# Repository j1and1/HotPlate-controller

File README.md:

# Hotplate reflow controller

This is still a work in progress, and controller code has issues of overshooting the target temperature **use at your own risk.** 

This is a implementation of temperature control of heated plate for reflow soldering.

## Wiring

To make this you will need:
1. Arduino pro mini (or any other microcontroller)
2. Thermal resistor (I used 100k one from my 3d printer spares)
3. 4.7kOhm resistor for temperature resistor pullup
4. 10uF capacitor for stabilizing sensor value
5. Nokia 5510 display module (Or other display module... code might need to be patched for this though)
6. Solid state relay (use solid state relay to avoid arking when Arduino enables disables the output pin)
7. if Arduino runs on 5V you will need additional 5 10k resistors and one 1kOhm resistors on the SPI line ment for display.

## Compiling code

To compile Arduino code you will need few additional libraries.
1. Thermistor library [from here](https://github.com/miguel5612/ThermistorLibrary) or Arduino IDE library section
2. Adafruit PCD8544 library from Arduino IDE library section [or here](https://github.com/adafruit/Adafruit-PCD8544-Nokia-5110-LCD-library). Dont forget to install dependencies for it too.

## Known issues
- Thermal runaway algorithm is ignoring the state of solid state relay output pin
- Controller code does not account for thermal mass of the heater and plate. This will get solved once PID algorithm is added.

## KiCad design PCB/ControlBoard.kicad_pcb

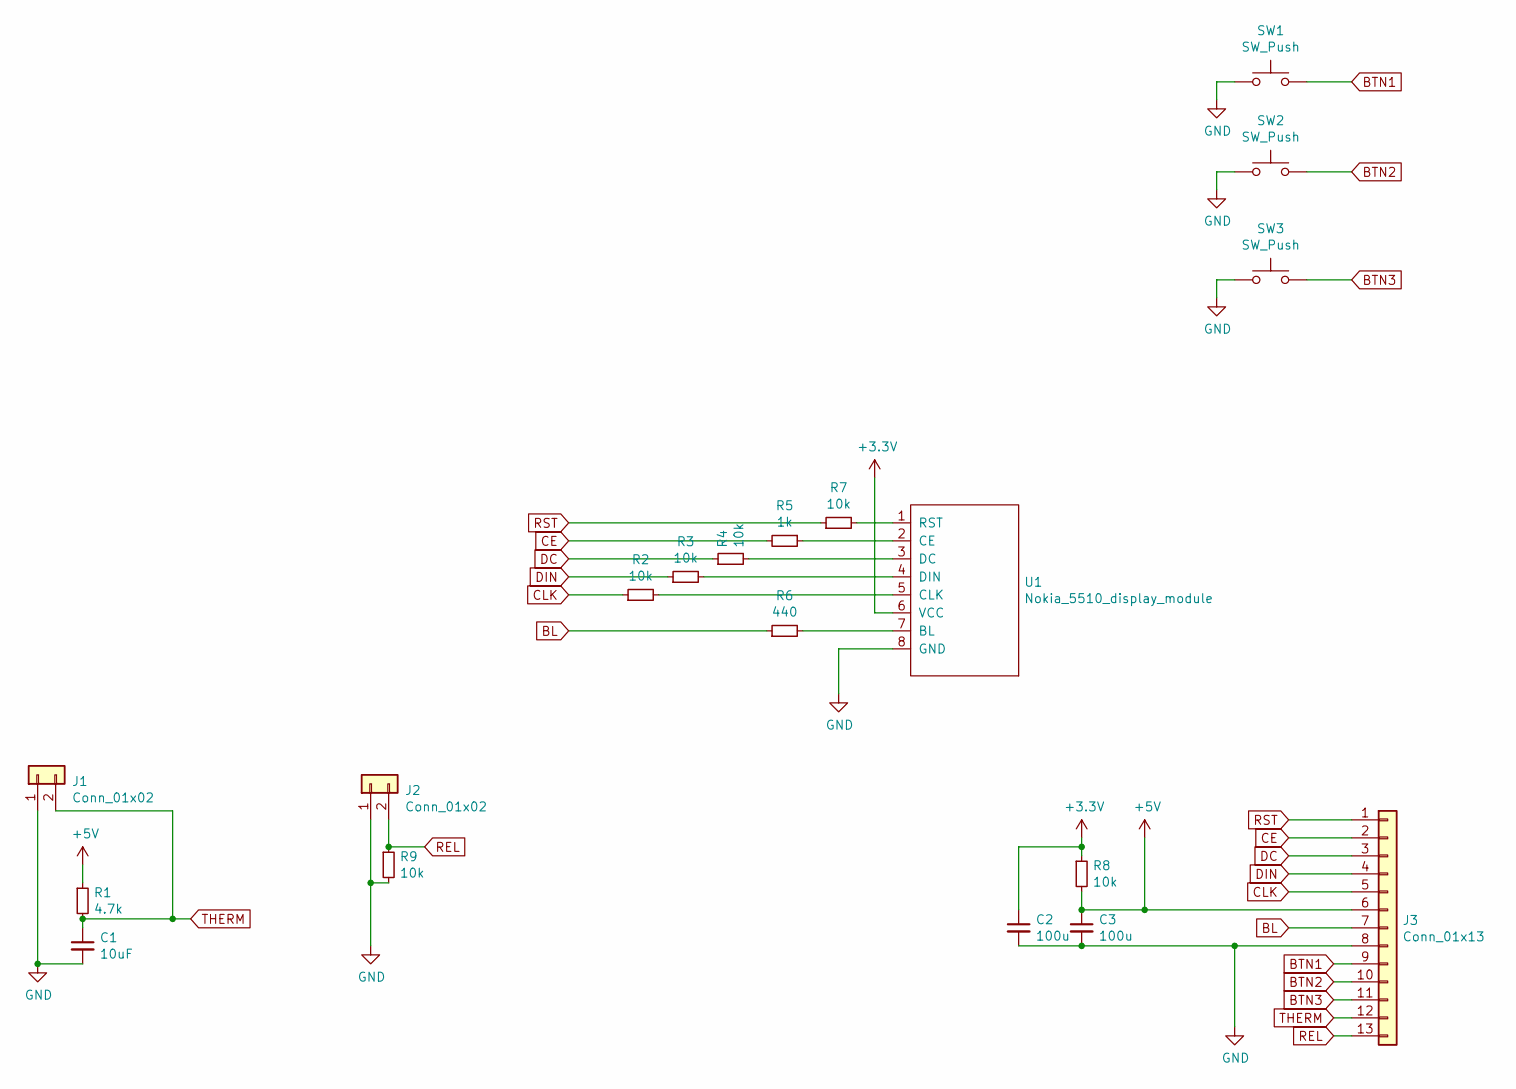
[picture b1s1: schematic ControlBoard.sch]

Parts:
C1: 10uF; C_0603_1608Metric_Pad1.08x0.95mm_HandSolder
C2, C3: 100u; C_0603_1608Metric_Pad1.08x0.95mm_HandSolder
J1, J2: Conn_01x02; PinHeader_1x02_P2.54mm_Horizontal
J3: Conn_01x13; PinHeader_1x13_P2.54mm_Vertical
R1: 4.7k; R_0402_1005Metric_Pad0.72x0.64mm_HandSolder
R2, R3, R4, R7, R8, R9: 10k; R_0402_1005Metric_Pad0.72x0.64mm_HandSolder
R5: 1k; R_0402_1005Metric_Pad0.72x0.64mm_HandSolder
R6: 440; R_0402_1005Metric_Pad0.72x0.64mm_HandSolder
SW1, SW2, SW3: SW_Push; SW_PUSH_6mm
U1: Nokia_5510_display_module; NOKIA_5510_display_module

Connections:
+3V3: C2.1, R8.1, U1.6 (VCC)
+5V: C3.1, J3.6, R1.1, R8.2
BL: J3.7, R6.1
BTN1: J3.9, SW1.2
BTN2: J3.10, SW2.2
BTN3: J3.11, SW3.2
CE: J3.2, R5.2
CLK: J3.5, R2.1
DC: J3.3, R4.1
DIN: J3.4, R3.1
GND: C1.2, C2.2, C3.2, J1.1, J2.1, J3.8, R9.2, SW1.1, SW2.1, SW3.1, U1.8 (GND)
unnamed: R2.2, U1.5 (CLK)
unnamed: R3.2, U1.4 (DIN)
unnamed: R4.2, U1.3 (DC)
unnamed: R5.1, U1.2 (CE)
unnamed: R6.2, U1.7 (BL)
unnamed: R7.2, U1.1 (RST)
REL: J2.2, J3.13, R9.1
RST: J3.1, R7.1
THERM: C1.1, J1.2, J3.12, R1.2

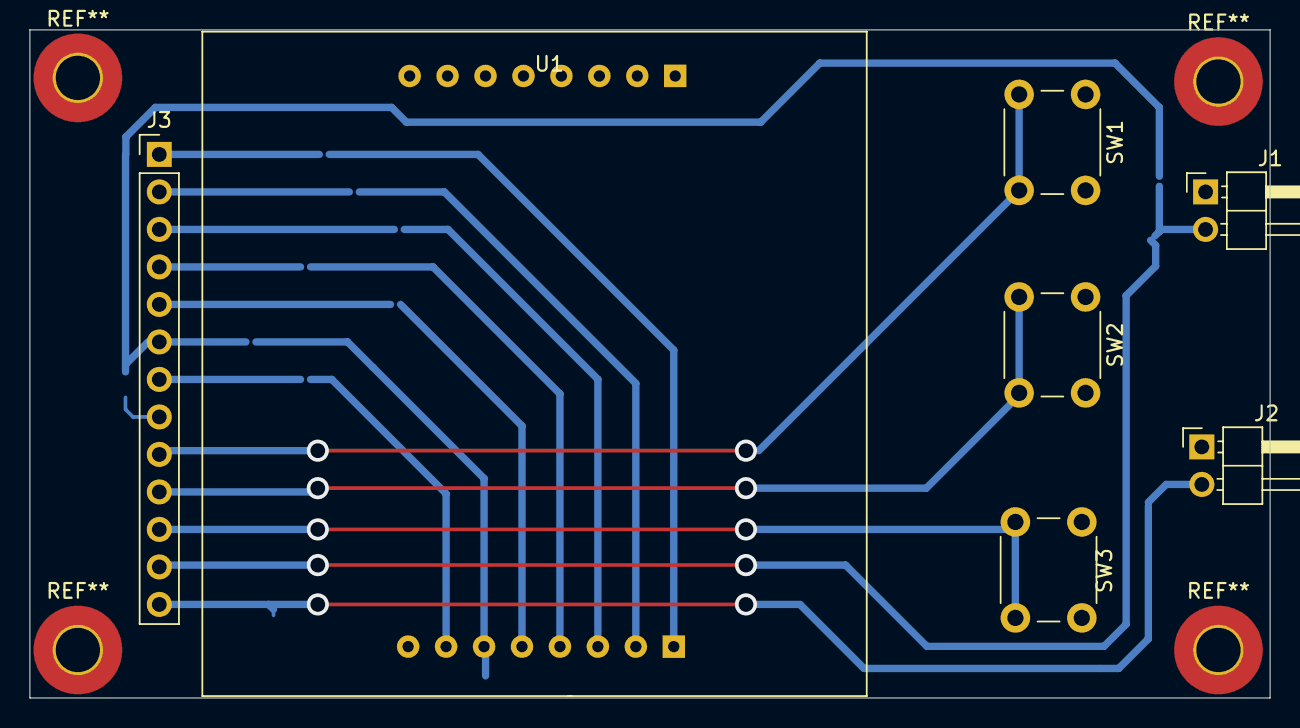
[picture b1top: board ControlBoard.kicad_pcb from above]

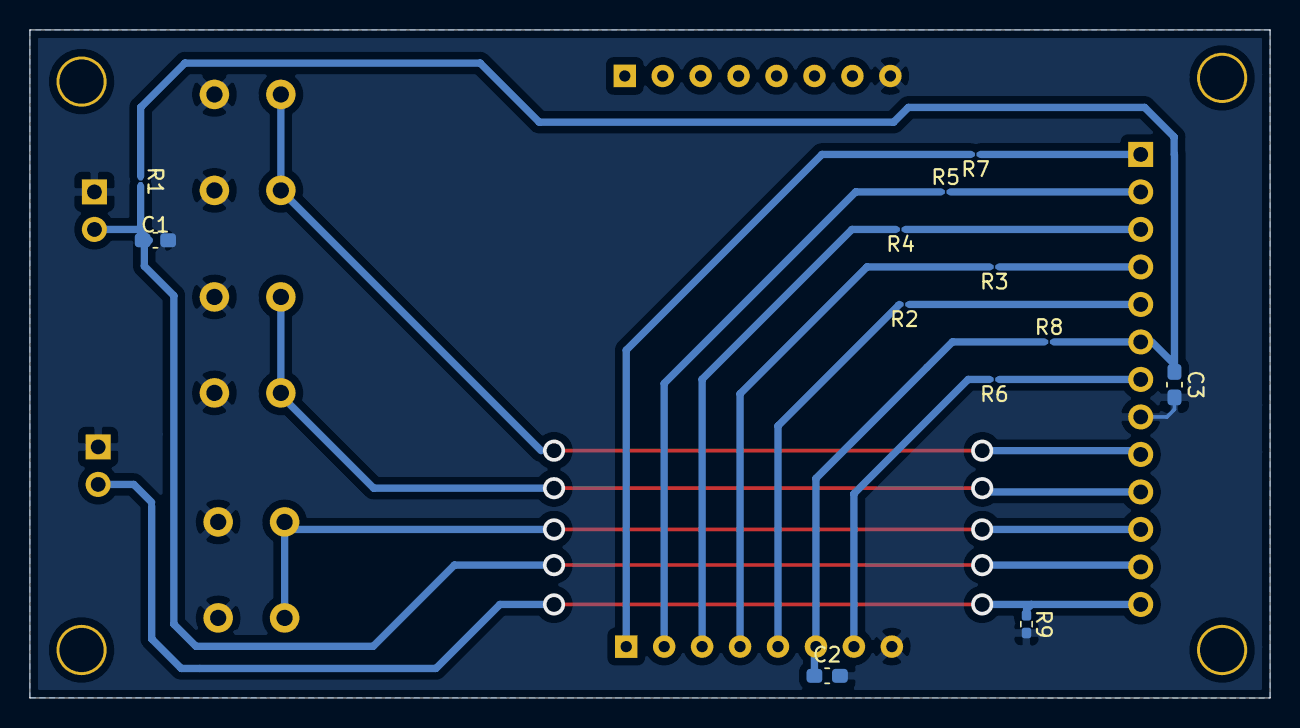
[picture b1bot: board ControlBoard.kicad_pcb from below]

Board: 2 copper layers, 84.0 x 45.2 mm, 19 parts (12 on the bottom side), 20 nets.

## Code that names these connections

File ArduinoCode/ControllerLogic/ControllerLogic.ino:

// Display includes -> Adafruit PCD8544 lib
#include <Adafruit_GFX.h>
#include <Adafruit_PCD8544.h>

#include "Configuration.h"
#include "TemperatureControl.h"

TemperatureControl tc;

// Display related variables
// Software SPI (slower updates, more flexible pin options):
// pin 13 - Serial clock out (SCLK)
// pin 11 - Serial data out (DIN)
// pin 9 - Data/Command select (D/C)
// pin 10 - LCD chip select (CS)
// pin 8 - LCD reset (RST)
Adafruit_PCD8544 display = Adafruit_PCD8544(13, 11, 9, 10, 8);

// menu related variables
int menuitem = 0;
int page = 0;

volatile boolean up = false;
volatile boolean down = false;
volatile boolean middle = false;

int downButtonState = 0;
int upButtonState = 0;  
int selectButtonState = 0;          
int lastDownButtonState = 0;
int lastSelectButtonState = 0;
int lastUpButtonState = 0;
// menu related stuff end

void setup() {
  // put your setup code here, to run once:
  pinMode(BTN1, INPUT_PULLUP);
  pinMode(BTN2, INPUT_PULLUP);
  pinMode(BTN3, INPUT_PULLUP);

  pinMode(OUT1, OUTPUT);
  digitalWrite(OUT1, LOW);

  Serial.begin(9600);

  // start display related activities
  display.begin();
  display.setContrast(50);
  display.display(); // show splashscreen
  delay(2000);
  display.clearDisplay(); // clears the screen and buffer
  display.setRotation(2);
}

void loop() {
  displayMenu();
  // check if thermal runaway
  if (tc.isThermalRunawayDetected())
  {
    page = 2;
  }
  else
  {
    doMenuAction();
  }
  tc.runLoop();
}

void displayMenu()
{
  if (page == 0) 
  {    
    display.setTextSize(1);
    display.clearDisplay();
    display.setTextColor(BLACK, WHITE);
    display.setCursor(15, 0);
    display.print("MAIN MENU");
    display.drawFastHLine(0,10,83,BLACK);
    display.setCursor(0, 15);
   
    if (menuitem==0) 
    { 
      display.setTextColor(WHITE, BLACK);
    }
    else 
    {
      display.setTextColor(BLACK, WHITE);
    }
    display.print(">Fixed Temp");
    display.setCursor(0, 25);

    if (menuitem==1) 
    { 
      display.setTextColor(WHITE, BLACK);
    }
    else 
    {
      display.setTextColor(BLACK, WHITE);
    }
    display.print(">Reflow curve");

    display.setTextColor(BLACK, WHITE);
    display.setCursor(0, 35);
    display.print("Temp C: ");
    display.print(tc.getLastTemp());
    display.display();
  }
  else if (page == 1) 
  {
    display.setTextSize(1);
    display.clearDisplay();
    display.setTextColor(BLACK, WHITE);
    display.setCursor(15, 0);
    display.print("Target temp:");
    display.drawFastHLine(0,10,83,BLACK);
    display.setCursor(5, 15);
    display.print("Value");
    display.setTextSize(2);
    display.setCursor(5, 25);
    display.print((int) tc.getTargetTemp());
 
    display.setTextSize(2);
    display.display();
  }
  else if (page == 2) // thermal runaway
  {
    display.setTextSize(1);
    display.clearDisplay();
    display.setTextColor(BLACK, WHITE);
    display.setCursor(15, 0);
    display.print("Error");
    display.drawFastHLine(0,10,83,BLACK);
    display.setCursor(5, 15);
    display.print("Thermal");
    display.setCursor(5, 25);
    display.print("runaway");
    display.display();
  }
  else
  {
    display.setTextSize(1);
    display.clearDisplay();
    display.setTextColor(BLACK, WHITE);
    display.setCursor(15, 0);
    display.print("Heating");
    display.drawFastHLine(0,10,83,BLACK);
    display.setCursor(5, 15);
    display.print("Time:");
    const unsigned long t = (millis() - tc.getHeaterStartTime()) / 1000;
    display.print(t);
    display.setCursor(5, 25);
    display.print("T:");
    display.print(tc.getLastTemp());
    display.print("/");
    display.print((int) tc.getTargetTemp());
    display.display();
  }
}

void doMenuAction()
{
  downButtonState = digitalRead(BTN3);
  selectButtonState = digitalRead(BTN2);
  upButtonState =   digitalRead(BTN1);

  checkIfDownButtonIsPressed();
  checkIfUpButtonIsPressed();
  checkIfSelectButtonIsPressed();

  if (up && page == 0 ) {
    up = false;
    menuitem--;
    if (menuitem== -1)
    {
      menuitem = 1;
    }      
  }
  else if (up && page == 1 ) 
  {
    tc.setTargetTemp(tc.getTargetTemp() + 1);
  }


  if (down && page == 0) {
    down = false;
    menuitem++;
    if (menuitem == 2) 
    {
      menuitem=0;
    }      
  }
  else if (down && page == 1) 
  {
    tc.setTargetTemp(tc.getTargetTemp() - 1);
  }

  if (middle) {
    middle = false;

    // set fixed temperature
    if (page == 0 && menuitem==0) {
      page = 1;
    }
    // reflow curve
    else if (page == 0 && menuitem == 1)
    {
      tc.setUseReflowCurve(true);
      tc.setIsHeating(true);
      page = 3;
    }
    // heat the 
    else if (page == 1) {
      tc.setUseReflowCurve(false);
      tc.setIsHeating(true);
      page = 3;
    }
    // disable heating and move back
    else
    {
      tc.setIsHeating(false);
      page = 0;
    }
  }
}

void checkIfDownButtonIsPressed()
{
  if (downButtonState != lastDownButtonState) 
  {
    if (downButtonState == 0) 
    {
      down = true;
    }
    else
    {
      down = false;
    }
    delay(50);
  }
  lastDownButtonState = downButtonState;
}

void checkIfUpButtonIsPressed()
{
  if (upButtonState != lastUpButtonState) 
  {
    if (upButtonState == 0) {
      up = true;
    }
    else
    {
      up = false;
    }
    delay(50);
  }
  lastUpButtonState = upButtonState;
}

void checkIfSelectButtonIsPressed()
{
  if (selectButtonState != lastSelectButtonState) 
  {
    if (selectButtonState == 0) {
      middle = true;
    }
    delay(50);
  }
  lastSelectButtonState = selectButtonState;
}

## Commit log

2022-03-30 Updated submodules with correct links
2022-03-31 Created rough placement of control board... need to recheck footprint sizes
2022-04-01 Board done
2022-04-04 Fixed some holes and footprints so I can mill this at home
2022-08-12 Initial commit of control code
2022-08-13 Moved the thermal control related code to separate files
2022-08-14 Controller board now controls stuff
2022-08-14 fix thermal runaway
2022-08-18 Added readme
2022-08-18 Add README.md and implement controller code
    * Initial commit of control code
    * Moved the thermal control-related code to separate files
    * Controller board now controls stuff
    * fix thermal runaway
    * Added readme
2023-02-04 Added PID for temperature control and moved to Platformio
